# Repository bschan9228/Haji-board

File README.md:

# Haji Keyboard
The Haji keyboard uses 8-bit shift registers, rather than the typical keyboard matrix cirucit. An advantage in using shift registers is that you can add any amount of keys, instead of being limited by the amount of I/O pins. It uses an STM32F1 chip to communicate to a computer using its native USB interface. I sourced components, designed and fabricated the pcb, soldered, built, and programmed a fully working prototype of a small macropad from scratch.

##PARTS
NOTES:
HOTSWAPPABLE SWITCHES

ICS:
STM32F1
74HC165D,653

MODULES:
UNIFIED C3

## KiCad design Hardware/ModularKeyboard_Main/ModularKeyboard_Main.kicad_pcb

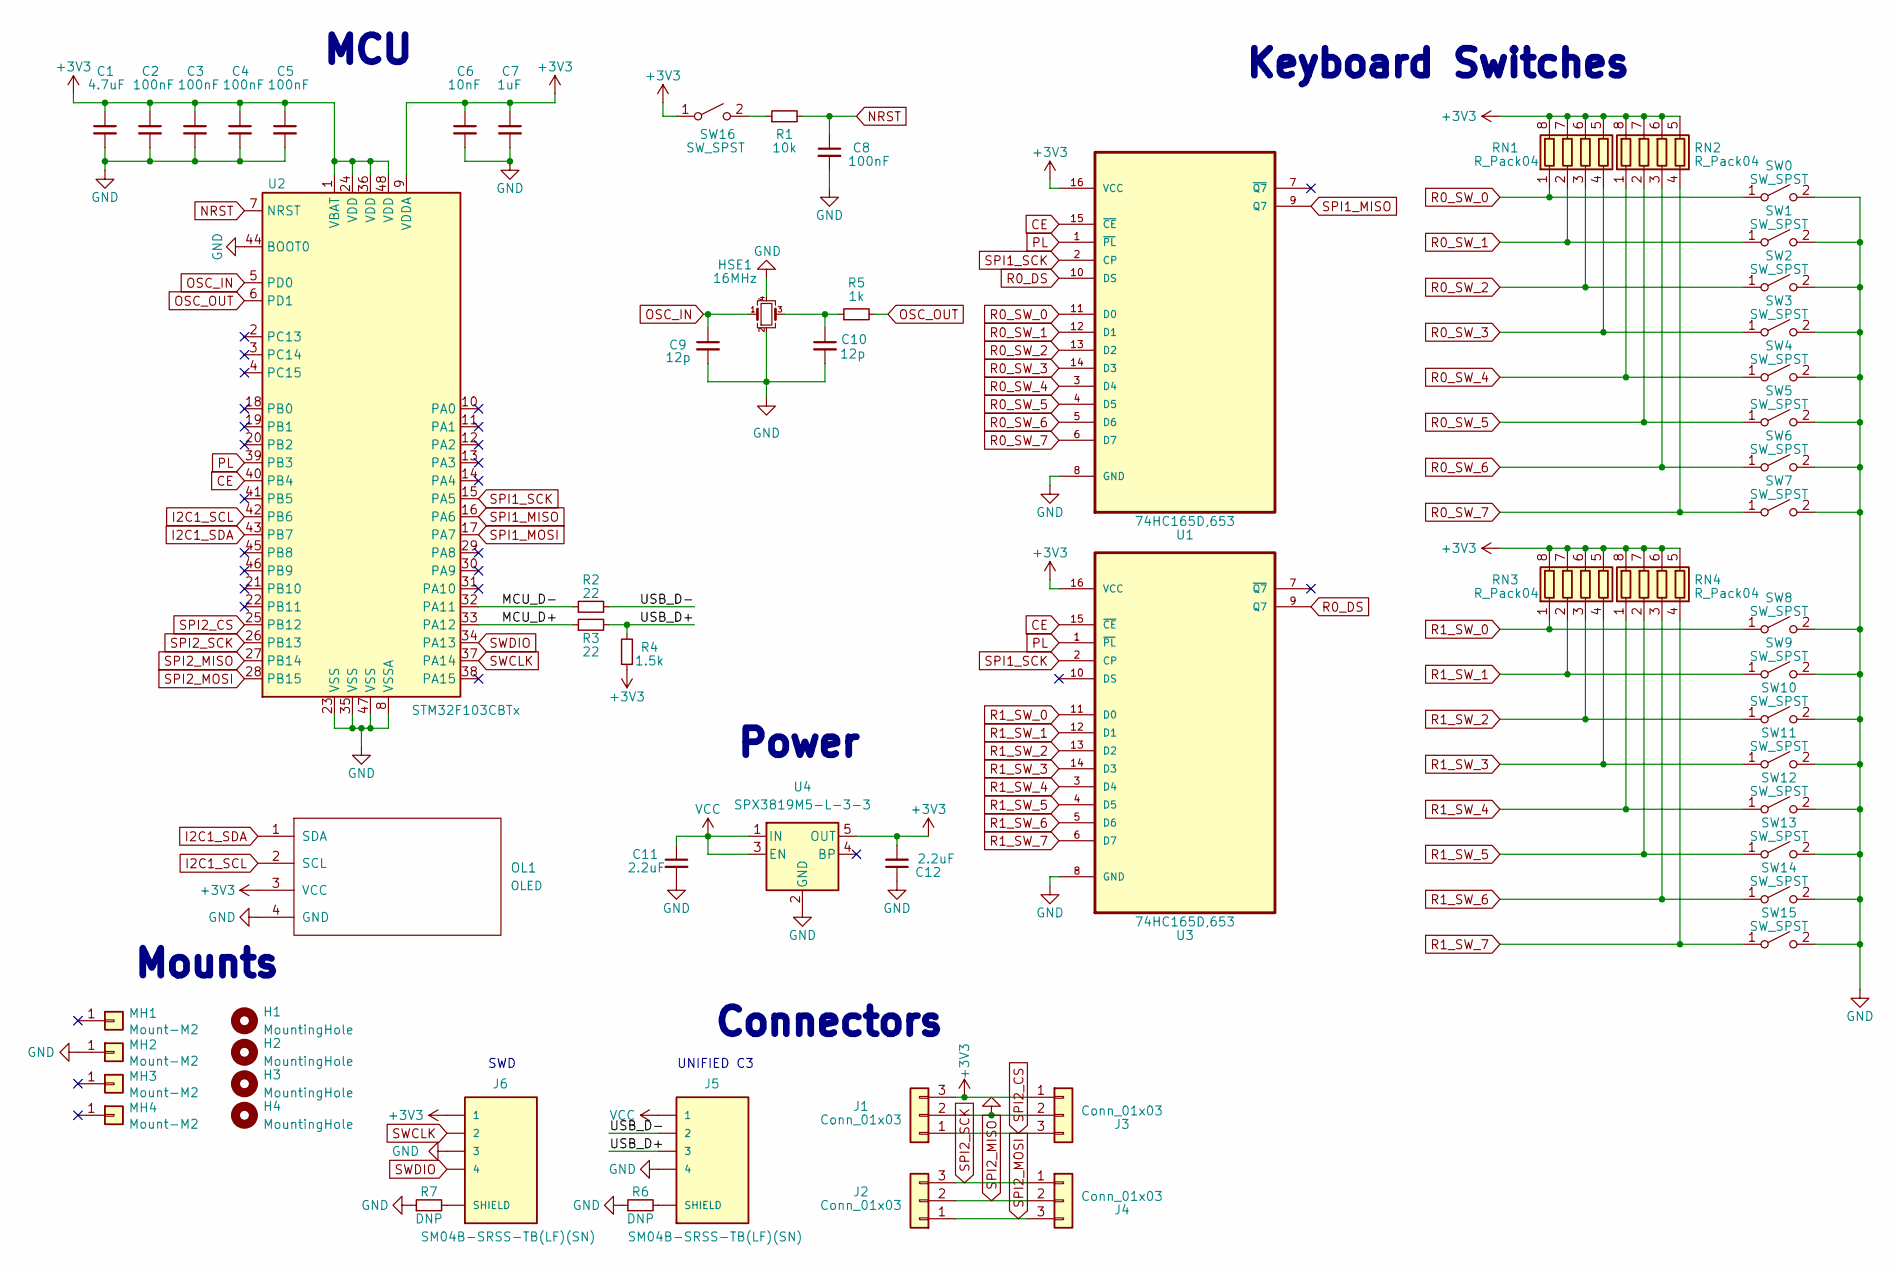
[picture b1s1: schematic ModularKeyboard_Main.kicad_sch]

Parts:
C1: 4.7uF; C_0402_1005Metric
C2, C3, C4, C5, C8: 100nF; C_0402_1005Metric
C6: 10nF; C_0402_1005Metric
C7: 1uF; C_0402_1005Metric
C9, C10: 12p; C_0402_1005Metric
C11, C12: 2.2uF; C_0402_1005Metric
H1, H2, H3, H4: MountingHole; MountingHole_2.2mm_M2
HSE1: 16MHz; Crystal_SMD_3225-4Pin_3.2x2.5mm
J1, J2, J3, J4: Conn_01x03; PG-3P-2.5
J5, J6: SM04B-SRSS-TB(LF)(SN); JST_SM04B-SRSS-TB(LF)(SN)
MH1, MH2, MH3, MH4: Mount-M2; Generic-Mounthole
OL1: OLED; OLED_v2
R1: 10k; R_0402_1005Metric
R2, R3: 22; R_0402_1005Metric
R4: 1.5k; R_0402_1005Metric
R5: 1k; R_0402_1005Metric
R6, R7: DNP; R_0402_1005Metric
RN1, RN2, RN3, RN4: R_Pack04; R_Array_Convex_4x0402
SW0, SW1, SW2, SW3, SW4, SW5, SW6, SW7, SW8, SW9, SW10, SW11, SW12, SW13, SW14, SW15: SW_SPST; MX-1U-NoLED
SW16: SW_SPST; SW_SPST_B3U-1000P
U1, U3: 74HC165D,653; SOIC127P600X175-16N; MPN 74HC165D,653
U2: STM32F103CBTx; LQFP-48_7x7mm_P0.5mm
U4: SPX3819M5-L-3-3; SOT-23-5

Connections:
+3V3: C1.1, C2.1, C3.1, C4.1, C5.1, C6.1, C7.1, C12.2, J1.3, J3.1, J6.1, OL1.3 (VCC), R4.1, RN1.5 (R4.2), RN1.6 (R3.2), RN1.7 (R2.2), RN1.8 (R1.2), RN2.5 (R4.2), RN2.6 (R3.2), RN2.7 (R2.2), RN2.8 (R1.2), RN3.5 (R4.2), RN3.6 (R3.2), RN3.7 (R2.2), RN3.8 (R1.2), RN4.5 (R4.2), RN4.6 (R3.2), RN4.7 (R2.2), RN4.8 (R1.2), SW16.1 (A), U1.16 (VCC), U2.1 (VBAT), U2.9 (VDDA), U2.24 (VDD), U2.36 (VDD), U2.48 (VDD), U3.16 (VCC), U4.5 (OUT)
/MCU_D+: R3.1, U2.33 (PA12)
/MCU_D-: R2.1, U2.32 (PA11)
/USB_D+: J5.3, R3.2, R4.2
/USB_D-: J5.2, R2.2
CE: U1.15 (~CE), U2.40 (PB4), U3.15 (~CE)
GND: C1.2, C2.2, C3.2, C4.2, C5.2, C6.2, C7.2, C8.2, C9.2, C10.2, C11.2, C12.1, HSE1.2, HSE1.4, J1.2, J3.2, J5.4, J6.3, MH2.1, OL1.4 (GND), R6.1, R7.1, SW0.2 (B), SW1.2 (B), SW2.2 (B), SW3.2 (B), SW4.2 (B), SW5.2 (B), SW6.2 (B), SW7.2 (B), SW8.2 (B), SW9.2 (B), SW10.2 (B), SW11.2 (B), SW12.2 (B), SW13.2 (B), SW14.2 (B), SW15.2 (B), U1.8 (GND), U2.8 (VSSA), U2.23 (VSS), U2.35 (VSS), U2.44 (BOOT0), U2.47 (VSS), U3.8 (GND), U4.2 (GND)
I2C1_SCL: OL1.2 (SCL), U2.42 (PB6)
I2C1_SDA: OL1.1 (SDA), U2.43 (PB7)
NRST: C8.1, R1.2, U2.7 (NRST)
unnamed: C10.1, HSE1.3, R5.1
unnamed: J5.S1 (SHIELD), J5.S2 (SHIELD), R6.2
unnamed: J6.S1 (SHIELD), J6.S2 (SHIELD), R7.2
unnamed: R1.1, SW16.2 (B)
OSC_IN: C9.1, HSE1.1, U2.5 (PD0)
OSC_OUT: R5.2, U2.6 (PD1)
PL: U1.1 (~PL), U2.39 (PB3), U3.1 (~PL)
R0_DS: U1.10 (DS), U3.9 (Q7)
R0_SW_0: RN1.1 (R1.1), SW0.1 (A), U1.11 (D0)
R0_SW_1: RN1.2 (R2.1), SW1.1 (A), U1.12 (D1)
R0_SW_2: RN1.3 (R3.1), SW2.1 (A), U1.13 (D2)
R0_SW_3: RN1.4 (R4.1), SW3.1 (A), U1.14 (D3)
R0_SW_4: RN2.1 (R1.1), SW4.1 (A), U1.3 (D4)
R0_SW_5: RN2.2 (R2.1), SW5.1 (A), U1.4 (D5)
R0_SW_6: RN2.3 (R3.1), SW6.1 (A), U1.5 (D6)
R0_SW_7: RN2.4 (R4.1), SW7.1 (A), U1.6 (D7)
R1_SW_0: RN3.1 (R1.1), SW8.1 (A), U3.11 (D0)
R1_SW_1: RN3.2 (R2.1), SW9.1 (A), U3.12 (D1)
R1_SW_2: RN3.3 (R3.1), SW10.1 (A), U3.13 (D2)
R1_SW_3: RN3.4 (R4.1), SW11.1 (A), U3.14 (D3)
R1_SW_4: RN4.1 (R1.1), SW12.1 (A), U3.3 (D4)
R1_SW_5: RN4.2 (R2.1), SW13.1 (A), U3.4 (D5)
R1_SW_6: RN4.3 (R3.1), SW14.1 (A), U3.5 (D6)
R1_SW_7: RN4.4 (R4.1), SW15.1 (A), U3.6 (D7)
SPI1_MISO: U1.9 (Q7), U2.16 (PA6)
SPI1_MOSI: U2.17 (PA7)
SPI1_SCK: U1.2 (CP), U2.15 (PA5), U3.2 (CP)
SPI2_CS: J1.1, J3.3, U2.25 (PB12)
SPI2_MISO: J2.2, J4.2, U2.27 (PB14)
SPI2_MOSI: J2.1, J4.3, U2.28 (PB15)
SPI2_SCK: J2.3, J4.1, U2.26 (PB13)
SWCLK: J6.2, U2.37 (PA14)
SWDIO: J6.4, U2.34 (PA13)
VCC: C11.1, J5.1, U4.1 (IN), U4.3 (EN)

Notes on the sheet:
Keyboard Switches
Connectors
SWD
UNIFIED C3
Power
Mounts
MCU

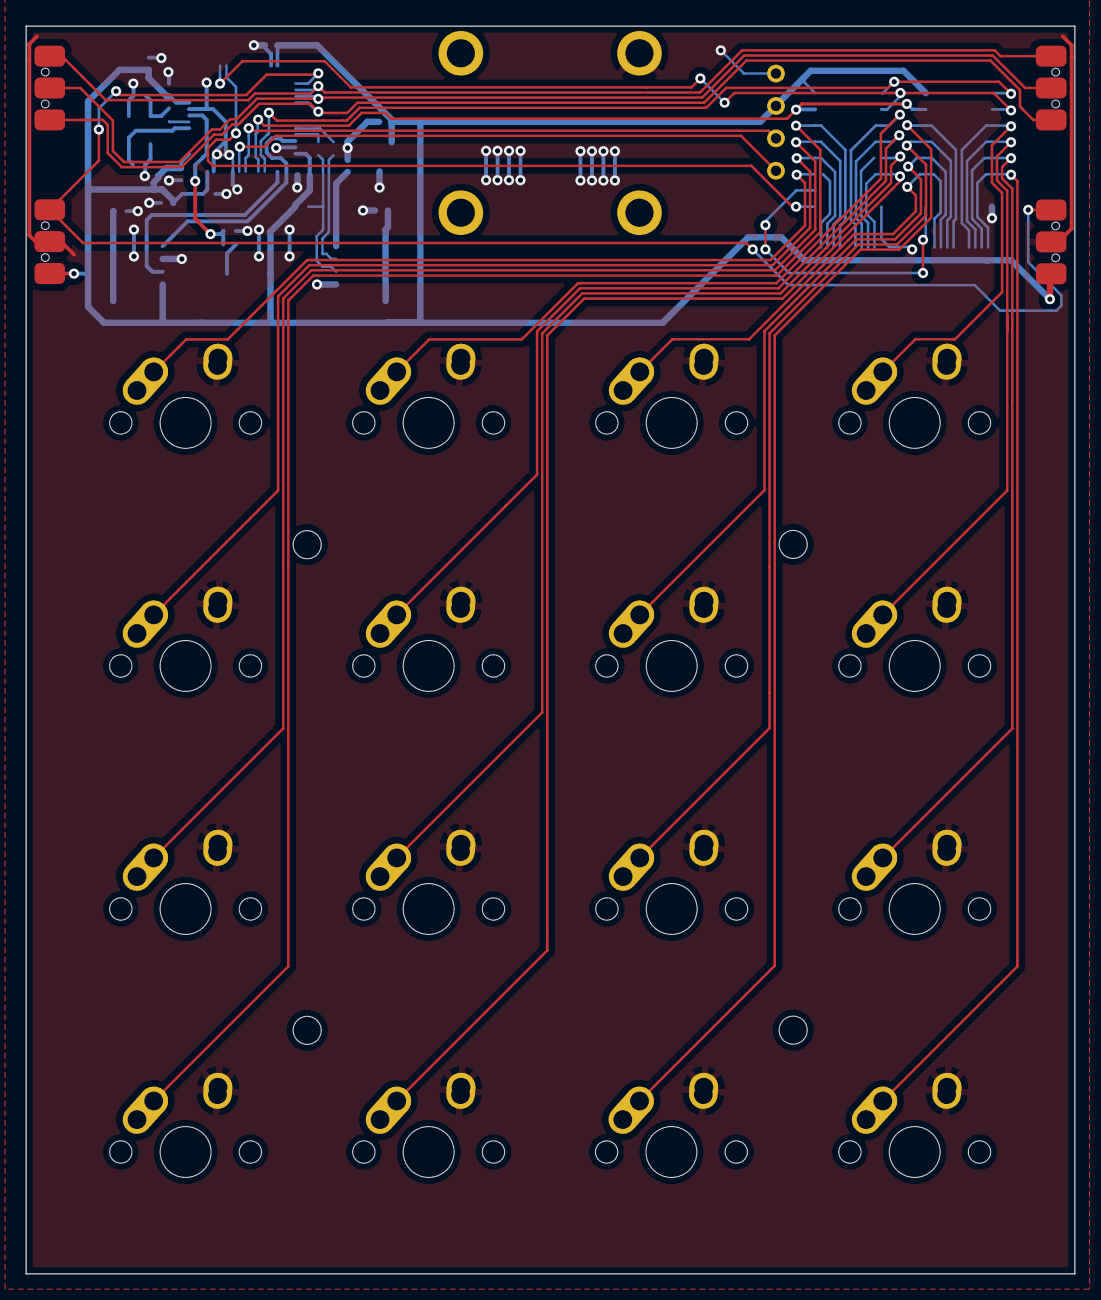
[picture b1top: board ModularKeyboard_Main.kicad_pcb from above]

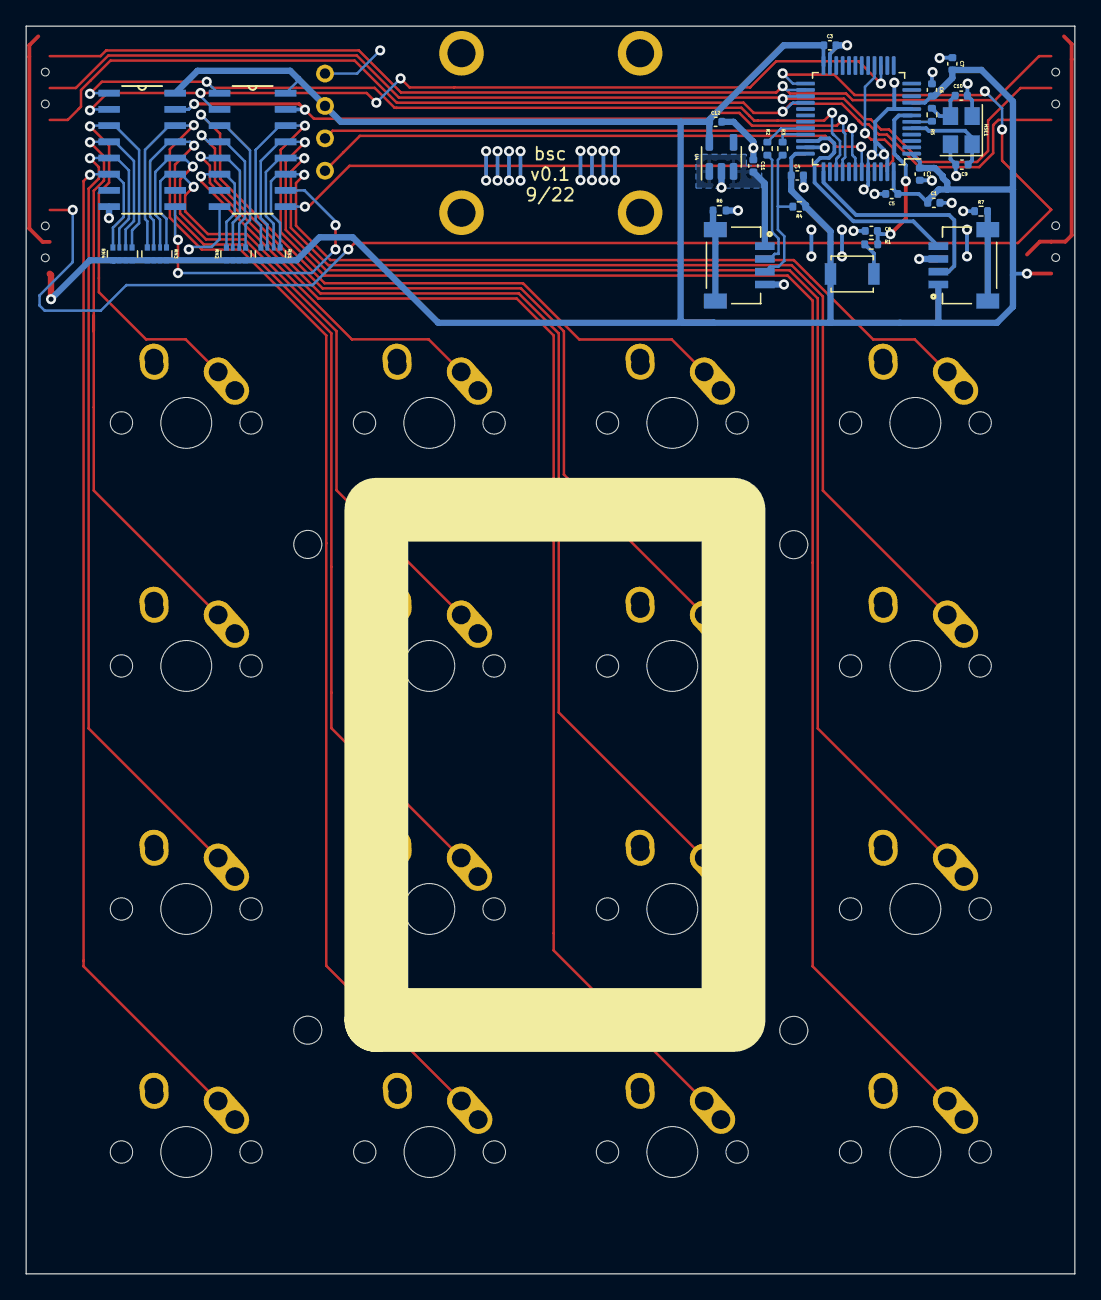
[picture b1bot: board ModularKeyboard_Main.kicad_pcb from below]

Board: 2 copper layers, 82.2 x 97.8 mm, 60 parts (31 on the bottom side), 43 nets.

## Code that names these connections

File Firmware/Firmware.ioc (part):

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Mcu.Name=STM32F103C(8-B)Tx
Mcu.Package=LQFP48
Mcu.UserName=STM32F103CBTx
PA11.Mode=Device
PA11.Signal=USB_DM
PA12.Mode=Device
PA12.Signal=USB_DP
PA13.Mode=Serial_Wire
PA13.Signal=SYS_JTMS-SWDIO
PA14.Mode=Serial_Wire
PA14.Signal=SYS_JTCK-SWCLK
PA5.Mode=Full_Duplex_Master
PA5.Signal=SPI1_SCK
PA6.Mode=Full_Duplex_Master
PA6.Signal=SPI1_MISO
PA7.Mode=Full_Duplex_Master
PA7.Signal=SPI1_MOSI
PB12.GPIOParameters=GPIO_Label
PB12.GPIO_Label=SPI2_CS
PB12.Signal=GPIO_Output
PB13.Mode=Full_Duplex_Master
PB13.Signal=SPI2_SCK
PB14.Mode=Full_Duplex_Master
PB14.Signal=SPI2_MISO
PB15.Mode=Full_Duplex_Master
PB15.Signal=SPI2_MOSI
PB3.GPIOParameters=GPIO_Label
PB3.GPIO_Label=CE
PB3.Signal=GPIO_Output
PB4.GPIOParameters=GPIO_Label
PB4.GPIO_Label=PL
PB4.Signal=GPIO_Output
PB6.Mode=I2C
PB6.Signal=I2C1_SCL
PB7.Mode=I2C
PB7.Signal=I2C1_SDA
PD0-OSC_IN.Mode=HSE-External-Oscillator
PD0-OSC_IN.Signal=RCC_OSC_IN
PD1-OSC_OUT.Mode=HSE-External-Oscillator
PD1-OSC_OUT.Signal=RCC_OSC_OUT
RCC.HSEDivPLL=RCC_HSE_PREDIV_DIV2
RCC.HSE_VALUE=16000000
RCC.SYSCLKFreq_VALUE=72000000
RCC.SYSCLKSource=RCC_SYSCLKSOURCE_PLLCLK
board=custom

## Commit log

2022-09-19 Finished initial sketches
2022-09-19 Completed most wiring
2022-09-20 Completed wiring v0.1 -- add bom
2022-09-25 Completed v0.1
